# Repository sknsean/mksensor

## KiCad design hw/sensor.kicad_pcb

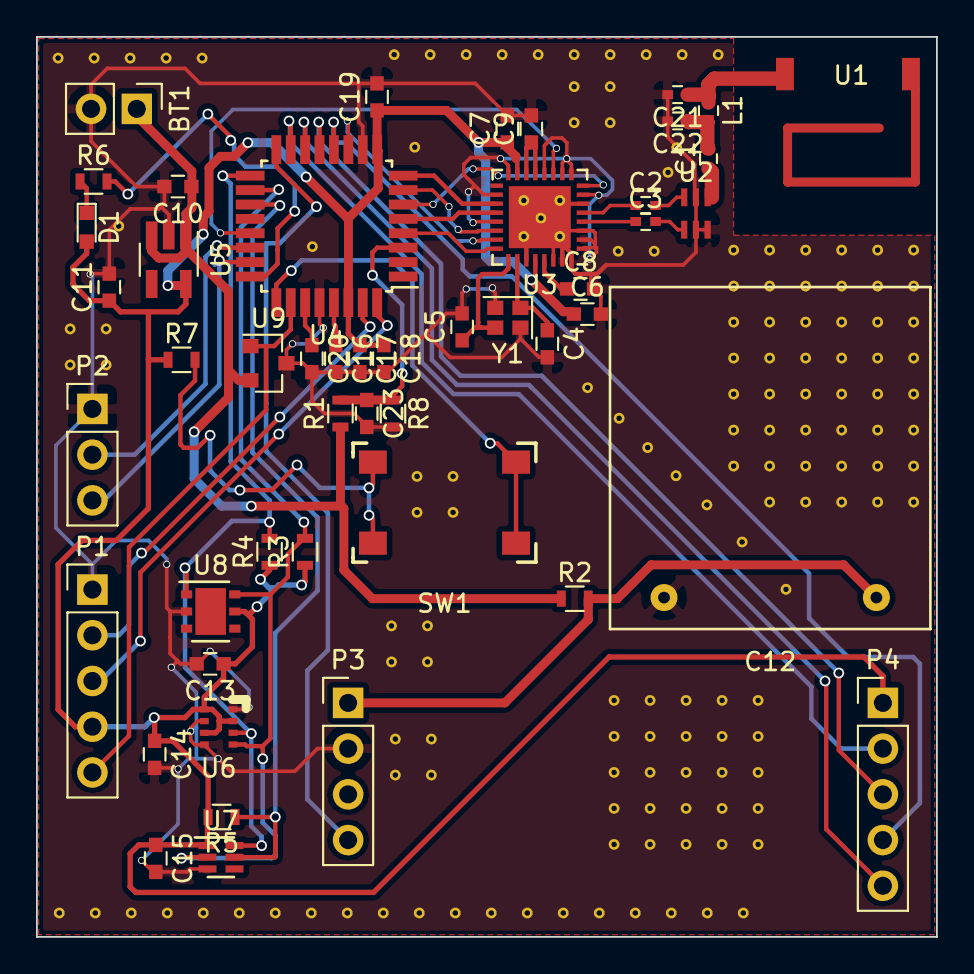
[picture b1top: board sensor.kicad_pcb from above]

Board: 2 copper layers, 50.0 x 50.0 mm, 49 parts (0 on the bottom side), 42 nets.

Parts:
BT1: Battery_Cell; Pin_Header_Straight_1x02_Pitch2.54mm
C1, C2, C3: 100pF; C_0402
C4, C5: 10pF; C_0603
C6, C7, C8, C9, C15, C16, C20: 1uF; C_0603
C10, C13, C14, C18, C19: 100nF; C_0603
C11, C23: C_Small; C_0603
C12: 0.47F; PM-5R0H474-R
C17: 10uF; C_0603
C21: 0.3pF; C_0402
C22: 3.9pF; C_0402
D1: LED_Small; LED_0603
L1: 18nH; R_0402
P1, P4: CONN_01X05; Pin_Header_Straight_1x05_Pitch2.54mm
P2: CONN_01X03; Pin_Header_Straight_1x03_Pitch2.54mm
P3: CONN_01X04; Pin_Header_Straight_1x04_Pitch2.54mm
R1, R8: R_Small; R_0603
R2: 39; R_0603
R3, R4: 1.5k; R_0603
R5: 10k; R_0603
R6: 330; R_0603
R7: 22k; R_0603
SW1: DTSM-61N
U1: 0868AT43A0020
U2: 0896FB15A0100
U3: AT86RF212B; QFN-32-1EP_5x5mm_Pitch0.5mm
U4: ATSAML21E18B; TQFP-32_7x7mm_Pitch0.8mm
U5: STLQ015; SOT-23-5_HandSoldering
U6: BMP280
U7: TSL25711
U8: HTU21D; DFN-6-1EP_3x3mm_Pitch0.95mm
U9: MIC1815; SOT-23
Y1: ECS-160-10-37-RWM-TR; Crystal_SMD_2016-4pin_2.0x1.6mm

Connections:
+3V3: C6.1, C7.1, C11.1, C13.1, C14.1, C15.1, C17.1, C18.1, C19.1, D1.2, P1.4, P4.1, R3.1, R4.1, R5.2, R7.1, U3.15, U3.28, U4.9, U4.30, U5.5, U6.2, U6.6, U6.8, U7.1, U8.5
+BATT: BT1.1, C10.1, R1.1, R2.1, U5.1, U5.3, U9.2
/Radio/RADIO_CS: U3.23, U4.11
/Radio/RADIO_IRQ: U3.24, U4.4
/Radio/RESET_RF: U3.8, U4.6
/Radio/SPI_CLK: U3.19, U4.8
/Radio/SPI_MISO: U3.20, U4.5
/Radio/SPI_MOSI: U3.22, U4.7
/cpu/CO2_EN_VBB: P4.2, U4.15
/cpu/CO2_RDY: P4.5, U4.14
/cpu/CO2_RESET: P3.4, U4.16
/cpu/I2C_SCL: R3.2, U4.18, U6.4, U7.2, U8.6
/cpu/I2C_SDA: R4.2, U4.17, U6.3, U7.6, U8.1
/cpu/LIGHT_IRQ: R5.1, U4.19, U7.5
/cpu/RADIO_SLP_TR: U3.11, U4.21
/sensors/CO2_RXD: P4.3, U4.13
/sensors/CO2_TXD: P4.4, U4.12
GNDD: BT1.2, C4.2, C5.2, C6.2, C7.2, C8.2, C9.2, C10.2, C11.2, C12.2, C13.2, C14.2, C15.2, C16.2, C17.2, C18.2, C19.2, C20.2, C21.2, C22.2, C23.2, P1.1, P2.1, P3.2, R8.2, U2.2, U2.5, U2.6, U3.1, U3.2, U3.3, U3.6, U3.7, U3.9, U3.10, U3.12, U3.16, U3.18, U3.21, U3.27, U3.30, U3.31, U3.32, U3.33, U4.10, U4.28, U5.2, U6.1, U6.5, U6.7, U7.3, U8.2, U9.3, Y1.2, Y1.4
unnamed: C1.1, U2.1
unnamed: C1.2, C22.1, L1.2
unnamed: C2.1, U3.5
unnamed: C2.2, U2.3
unnamed: C3.1, U3.4
unnamed: C3.2, U2.4
unnamed: C4.1, U3.26, Y1.1
unnamed: C5.1, U3.25, Y1.3
unnamed: C8.1, U3.29
unnamed: C9.1, U3.13, U3.14
unnamed: C12.1, P3.1, R2.2
unnamed: C16.1, U4.29
unnamed: C20.1, U4.27
unnamed: C21.1, L1.1, U1.1
unnamed: C23.1, R1.2, R8.1, U4.3
unnamed: D1.1, R6.1
unnamed: P1.2, U4.31
unnamed: P1.3, U4.32
unnamed: P2.2, U4.22
unnamed: P2.3, U4.23
unnamed: R6.2, U4.24
unnamed: R7.2, SW1.1, SW1.2
unnamed: SW1.3, SW1.4, U4.25
RESET: P1.5, U4.26, U9.1

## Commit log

2017-03-02 add initial schematic
2017-03-02 hw: add datasheets
2017-03-07 hierarchical and added debug port
2017-03-08 custom.lib: add STLQ015 ldo
2017-03-09 add wires and hierarchical labels
2017-03-09 anotate schematic (maybe too early)
2017-03-09 add sqtl015
2017-03-09 add BME280 baro, hum and temp sensor datasheet
2017-03-09 add htu21d symbol
2017-03-09 add htu21d to sensors schematic
2017-03-09 annotate
2017-03-09 add i2c labels
2017-03-10 custom.lib add balun and antenna
2017-03-10 annotate, radio values, new wires, add balun and antenna
2017-03-10 add bmp280 datasheet
2017-03-10 add LP8 datasheet
2017-03-10 add TSL2571 datasheet
2017-03-10 add at86rf212b datasheet
2017-03-10 custom.lib: add BMP280 barometer
2017-03-10 add TSL25711 lightsensor
2017-03-10 add sensor connections, tsl25711, co2 lp8 connectors, bmp280
2017-03-10 add vbatt for use in CO2 measurement
2017-03-10 add a lot cpu connections, correct footprint for cpu
2017-03-13 add custom footprints
2017-03-13 cpu wire up
2017-03-13 at86rf212 symbol fixups
2017-03-13 fixed radio crystal
2017-03-13 add crystal datasheet
2017-03-13 add htu21d datasheet
2017-03-13 add supercap datasheet
2017-03-13 add bmp280 footprint
2017-03-13 first draft of pcb
2017-03-13 add link to custom footprints
2017-03-15 custom.lib: add push button
2017-03-15 annotate, add button, add led
2017-03-15 add button datasheet
2017-03-15 add supervisor ic datasheet
2017-03-15 add LED datasheet
2017-03-15 complete routing
2017-03-16 add battery voltage to adc, annotate
2017-03-16 netlist prepare for tag
2017-03-16 add battery voltage to adc and thicker traces for radio
2017-03-16 add stiching via
2017-03-16 added a lot of stiching
2017-03-16 add production gerber
2017-03-17 add missing edge cuts to manufacture
2017-03-21 add bottom solder mask
2017-03-21 added dual sided print with components top and bottom
2017-05-12 datasheet: added SamD20
2017-05-12 cpu.sch: swapped RX/TX to CO2
2017-05-12 PM-5R0H: fixed pinout
2017-05-12 fixed Supercap footprint, add more stiching, fixed uart to co2 sensor
